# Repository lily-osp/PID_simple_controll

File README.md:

# BLDC Motor PID Controller (ESP32-C3)

Fixed-target PID controller for BLDC motors on the ESP32-C3, run bare-metal
for compute (no WiFi, no BLE). Holds 1440 RPM via a 200Hz FreeRTOS loop.

> History: this project previously shipped Arduino Uno and ATtiny85 variants.
> They were removed on 2026-10-31 (commit `396ade7`) and remain in git history.

## Overview

Single-platform implementation targeting the ESP32-C3 SuperMini. The C3 is
used for its 160MHz RISC-V core and hardware FPU; no wireless stack is used.
Two firmware builds share one set of drivers: a bench build for bring-up and
a production build for the enclosure.

| Build | Status | Use Case | Key Features |
|-------|--------|----------|--------------|
| **`esp32-c3/control/`** | Bench | Bring-up, service, Hall-line trials | Serial console, telemetry, trial scoring |
| **`esp32-c3/embedded/`** | Production | Enclosure deployment | Silent, autonomous, arming + stall failsafe |

## Key Features

- **200Hz Control Loop**: High-frequency PID updates via dedicated FreeRTOS task
- **Hardware-Accelerated PWM**: ESP32 LEDC peripheral generating smooth 5kHz motor control signals
- **Interrupt-Driven RPM**: High-precision pulse counting using IRAM-resident ISR
- **Sliding Window Filter**: 12-sample window + IIR smoothing for stable control input
- **ESC Arming + Soft-Start**: 2s zero-throttle arm, then 1.5s power ramp
- **FPU Utilization**: Full floating-point PID calculations for maximum precision
- **Safety Features**: Stall failsafe, emergency stop, input validation

## Quick Start

### 1. Hardware Requirements

- ESP32-C3 SuperMini (or compatible) + USB-C cable
- 3-Phase BLDC Motor with Hall Effect sensors
- PWM-compatible ESC / motor driver (e.g., JYQD V7.3E)
- Power supply appropriate for motor voltage requirements
- Voltage divider (2.2kΩ/3.3kΩ) if using 5V Hall sensors

### 2. Installation Steps

```bash
git clone https://github.com/your-repo/PID_simple_controll.git
cd PID_simple_controll
```

**Configure for your motor**:
1. Edit `esp32-c3/control/config.h` (pins, motor, PPR)
2. Edit `esp32-c3/control/config_common.h` (PID gains)
3. Configure pin assignments if using custom wiring

**Upload firmware**:
- Use Arduino IDE with ESP32 board support, or `arduino-cli`:

```bash
arduino-cli compile -b esp32:esp32:nologo_esp32c3_super_mini esp32-c3/embedded
arduino-cli upload  -p /dev/ttyACM0 -b esp32:esp32:nologo_esp32c3_super_mini esp32-c3/embedded
```

Which build to flash: see [esp32-c3/BUILDS.md](esp32-c3/BUILDS.md).

## Platform Details

### ESP32-C3 (`esp32-c3/`)

**Processor**: RISC-V @ 160MHz with hardware FPU

**Firmware Builds**:

**Bench (`control/`)**: Serial console for bring-up and service.
- Command parser, telemetry, diagnostics console
- Trial log auto-scores each power cycle to rank Hall permutations
- Full visibility into PID state and RPM estimation

**Production (`embedded/`)**: Silent, autonomous build for the enclosure.
- Control loop, ESC arming, soft-start, stall failsafe
- Shares the exact RPM estimator, PID, and LEDC drivers with the bench build

**Features**:
- Hardware FPU for fast floating-point calculations
- FreeRTOS ensures deterministic timing
- 3.3V logic level (requires voltage divider for 5V sensors)
- Comprehensive debugging via Serial Monitor (bench build)

Full architecture: [esp32-c3/README.md](esp32-c3/README.md).

### Custom Driver PCB (`PCB/V1/`)

Full-integration **64 × 98 mm, 4-layer** board combining the firmware above with its own
driver hardware — no external ESC needed:

- **JYQD-V7.3E3 architecture**: JY01 controller + JY213L gate driver + JY2605M
  half-bridges (same silicon as the reference driver board)
- **ESP32-C3 Super Mini** onboard as the controller (FG/PWM/VR/EL/trim pot)
- **Hall signal conditioner**: RC filter → LM324 (×11) → 74HC14 Schmitt trigger
- **Power tree**: V_IN → 7812 → +12V → 7805 → +5V

Design files, port pinouts, and build scripts: [PCB/V1/README.md](PCB/V1/README.md).
Bring-up procedure: [PCB/V1/TESTPLAN.md](PCB/V1/TESTPLAN.md).

## Documentation

### Comprehensive Guides

- **[Hardware Assembly Guide](docs/howto.md)**: Wiring guide, pin assignments, and connection diagrams
- **[Bench Wiring — stock JYQD + ESP32](docs/bench_wiring.md)**: Run the firmware on a stock JYQD-V7.3E3 and a bare Super Mini, before the custom PCB
- **[Troubleshooting Guide](docs/mitigation.md)**: Comprehensive diagnosis and solutions for common issues
- **[ESP32-C3 README](esp32-c3/README.md)**: Architecture, firmware, and hardware setup
- **[Builds](esp32-c3/BUILDS.md)**: Production vs bench firmware, and how they share code
- **[Diagnostics Guide](esp32-c3/DIAGNOSTICS.md)**: Serial console commands and fault isolation
- **[Driver PCB](PCB/V1/README.md)**: 64 × 98 mm 4-layer ESP32-C3 + JYQD-architecture driver board
- **[PCB Test Plan](PCB/V1/TESTPLAN.md)**: Staged bring-up procedure and failure diagnosis

## Configuration

### Motor Configuration

Settings live in `esp32-c3/*/config.h`:

```cpp
#define PULSES_PER_REV  4     // Set based on motor pole count
#define DEFAULT_TARGET_RPM 1440.0  // Target speed in RPM
```

**Calculating PULSES_PER_REV**: For a motor with N poles using single Hall sensor: `PULSES_PER_REV = N / 2`

Example: 8-pole motor = 4 pulses per revolution

### PID Tuning

PID constants are defined in `esp32-c3/control/config_common.h`:

```cpp
#define DEFAULT_KP  0.150  // Proportional gain
#define DEFAULT_KI  0.080  // Integral gain
#define DEFAULT_KD  0.015  // Derivative gain
```

**Tuning Process**:
1. Begin with Kp only (set Ki and Kd to 0)
2. Increase Kp until oscillation occurs, then reduce by 30%
3. Add Ki gradually to eliminate steady-state error
4. Add small Kd if overshoot occurs
5. Watch the bench console telemetry to verify stability

## Safety Considerations

1. **Electrical Isolation**: Keep logic power separate from motor power (common ground only)
2. **Voltage Protection**: Use voltage dividers when interfacing 5V sensors with 3.3V logic
3. **Mechanical Safety**: Secure motor firmly and remove propellers during initial testing
4. **Emergency Stop**: Keep power disconnect easily accessible during testing
5. **Current Rating**: Ensure power supply can handle motor startup current (typically 2-3x running current)
6. **Thermal Management**: Monitor ESC and motor temperatures during extended operation

## Troubleshooting Quick Reference

| Issue | Likely Cause | Solution |
|-------|--------------|----------|
| Motor doesn't start | Insufficient PWM threshold | Increase `PWM_MIN_THRESHOLD` to 60-80 |
| RPM reading 2x actual | Wrong `PULSES_PER_REV` | Divide current value by 2 |
| Unstable speed | Poor PID tuning or noise | Reduce Kp by 30%, add filtering |
| Random RPM spikes | Electrical noise | Add 0.1µF capacitor to Hall input |
| ESP32-C3 damaged | 5V applied to GPIO | Use voltage divider for all 5V signals |

See [Troubleshooting Guide](docs/mitigation.md) for comprehensive solutions.

## Contributing

Contributions are welcome. Areas of interest:
- Advanced PID algorithms (adaptive, fuzzy logic)
- Enhanced filtering techniques
- PCB designs for production deployment
- Test cases and validation procedures

Please read [CONTRIBUTING.md](CONTRIBUTING.md) for guidelines.

## License

MIT License - See [LICENSE](LICENSE) file for details.

This project is provided as-is for educational and commercial use. No warranty is provided for fitness for any particular purpose.

## Support

- **Issues**: Report bugs and request features via GitHub Issues
- **Discussions**: Ask questions and share experiences in GitHub Discussions
- **Documentation**: Comprehensive guides available in `docs/` directory

## Acknowledgments

Built with focus on reliability, performance, and practical deployment. Tested in real-world applications across multiple motor types and configurations.

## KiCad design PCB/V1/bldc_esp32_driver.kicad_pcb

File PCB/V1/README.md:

# BLDC Motor Driver — JYQD-V7.3E3 Architecture + ESP32-C3 Super Mini + Hall Amp

Custom **64 × 98 mm, 4-layer** PCB (full-integration) based on the **JYQD-V7.3E3** brushless driver
architecture, with an **ESP32-C3 Super Mini** controller and a Hall sensor signal
conditioner (RC filter → LM324 gain ×11 → 74HC14 Schmitt trigger).

> `JYQD-V7.3E3-English.pdf` is a product datasheet (specs + wiring), not a schematic.
> The circuit uses the JY IC family — **JY01** (SOP-16 controller), **JY213L** (TSSOP-20
> 3-phase gate driver), **JY2605M** (DFN-8 dual-NMOS half-bridge) — the same silicon as
> the reference board.

## External interface (fully integrated — 3 connectors only)

Everything else is handled on-board by the ESP32 (speed/direction/enable are driven
internally to the JY01). No control port, no GPIO breakouts.

| Connector | Pins | Function | Pitch |
|---|---|---|---|
| **J5** power | `P+  P−` | +12 V (V_IN) and ground | 5.00 mm (MaiXu MX126) |
| **J6** motor | `MA  MB  MC` | phase A / B / C to BLDC | 5.00 mm (MaiXu MX126) |
| **J3** Hall | `GND  Hc  Hb  Ha  5V` | Hall sensors (powered from 5 V) | 2.54 mm |

## Architecture

```
 V_IN ── 7812 ── +12V ── 7805 ── +5V
   │                │          │
 JY01 ──gate R── JY213L ──gate R── JY2605M ×3 ── phases A/B/C (J6)
   │                │
 Hall amp (5V): RC → LM324(×11) → 74HC14 → JY01 Hall inputs
 ESP32-C3: FG (scaled) / PWM → VR / EL / trim pot
```

- **Power tree**: `V_IN` (J5 P+) → U8 L7812 → `+12V` (gate-driver VCC) → U7 L7805 →
  `+5V` (logic). Hall amp runs on **+5V**, so 74HC14 outputs drive JY01 directly.
- **Current sense**: P− passes through R1 shunt (R005, 2512) to GND; JY01 `Is` sees the
  filtered shunt node (`ISENSE_F` via R36 + C21). *Caveat:* verify scaling against the
  driver's internal sense topology before relying on current limit.

## Design notes

- **78xx regulators**: with 12–36 V input keep `V_IN ≤ 28 V` for dropout/power margin
  (12 V nominal recommended).
- **PWM → VR**: GPIO1 drives the JY01 `VR` node through **R7 (100 Ω)**, directly. The
  JYQD datasheet accepts PWM 1–20 kHz on `VR` and averages it internally, so no level
  shifter is needed. Max drive is 3.3 V of the 0.1–5 V range ≈ 66 % speed.
- **GPIO4 → EL level shift**: EL is pulled up to **+5V** (R33 10 kΩ); GPIO4 drives it
  open-drain through R34 (1 kΩ). Configure GPIO4 as open-drain in firmware. Per the
  JYQD datasheet, EL high/floating **allows** operation and GND forbids it, so the
  motor is enabled by default at power-up.
- **FG scaling**: JY01 FG (5 V) → R4 2.2 k / R5 3.3 k divider → GPIO0 (RPM in, 3.3 V).
- **ESP32 pin usage**: GPIO0=RPM (FG), GPIO1=PWM→VR, GPIO2=**unconnected** (boot
  strapping pin, internal pull-up holds it high), GPIO3=trim ADC (ADC1_CH3),
  GPIO4=EL (open-drain), GPIO5=ERR LED. GPIO6–10/20/21 are spare/unconnected.
- **ERR LED** driven from GPIO5 via R32 (560 Ω); **PWR LED** from +5V via R20 (560 Ω).

## Pre-order audit

Checks performed on the exact fabrication data (`fab/`), all passing:

| Check | Result |
|---|---|
| DRC (`--severity-all`) | 0 violations, 0 unconnected items |
| Schematic parity | 0 genuine (266 cosmetic: root-sheet `/` prefix, footprint lib prefix) |
| Outline closure | closed Edge.Cuts loop, 0 open endpoints, 64.1 × 98.1 mm |
| Pads outside outline | 0 |
| Orphan nets (1 pad) | none |
| Fab files | 11 gerbers (4 copper) + 1 drill (Excellon, metric, decimal) + job file |
| Solder mask | 238 front / 33 rear openings (205 SMD + 29 THT + 4 NPTH); 0.05 mm expansion, 0.10 mm min web |
| Paste | 205 front apertures (1:1 with the SMD pads), none on the rear |

### Electrical fixes applied at audit

- **Bootstrap caps C13–C15 were 10 µF/25 V.** The `VB_x` rail floats on the phase and
  peaks at `V_IN + (V_+12V − V_f)` ≈ **V_IN + 11.3 V**. At the intended 12 V input that
  is 23.3 V (93 % of the rating); at 24 V input it is 35.3 V and the part fails short,
  taking the JY213L with it. Changed to **1 µF/50 V**, which is also the correct
  bootstrap value for this gate charge (droop ≈ Q_g/C ≈ 50 mV/cycle). Footprint
  unchanged (0805).
- **Unrated 0805 caps on rails** were given explicit ratings: `C12 → 10 µF/25 V` (it sits
  on +12 V), `C11/C19/C20 → 100 nF/50 V`.

### Layout changes applied at audit

1. **Trim pot moved off the strapping pin.** `RV1`'s wiper was on `GPIO2`, one of the
   three ESP32-C3 strapping pins (GPIO2/8/9), which must be high or floating at boot. The
   pot pulls it to 0 V at the low end of travel, so a power cycle with the pot turned
   down could enter joint-download boot instead of running firmware. The net now goes to
   `GPIO3` (`ADC1_CH3`, not a strapping pin); only the final 1.31 mm stub was rerouted,
   the 20 mm trunk is untouched. `GPIO2` is left floating, which is exactly the state its
   internal boot pull-up wants.
2. **Firmware followed the pin move.** `POT_SENSITIVITY_PIN` is now 3 and the
   `POT_ENABLE_PIN` gate is gone — the trim is always active and the pot midpoint is
   1.0×. Previously the firmware expected the enable on `GPIO3` while the board left it
   unconnected, so the pot did nothing at all. Both sketches compile (`pio run`,
   espressif32 7.0.1): control 17.9 % flash / 4.3 % RAM, embedded likewise.
3. **Four M3 mounting holes added** at the corner-arc centres (5 mm from each edge),
   NPTH 3.2 mm, marked board-only so they do not appear as schematic-parity extras, with
   a 1.2 mm copper-free ring so a screw head cannot short the GND pour.
4. **`C4` shifted 2.4 mm left** because its 10 mm can sat 0.4 mm from the bottom-right
   hole — an M3 head would have fouled it. Its three track endpoints were snapped to the
   new pad positions; nothing else moved.

### Remaining note

- **`EL` (GPIO4) and the ERR LED (GPIO5) are wired but unused by firmware.** `EL` is
  pulled to +5 V through R33 and driven open-drain through R34, so the JY01 enable state
  at power-up depends on the EL polarity of the JY01 itself — confirm before relying on
  the motor being disabled at boot. Wiring either up is a firmware change only.

## Status

**Folder layout:** `PCB/V1/` is this board. When a smaller revision is attempted it goes
in `PCB/V2/` alongside it, so both stay buildable and comparable.

**The previous board is preserved at git tag `v1`** (commit 837cf5a): 70 × 120 mm,
2 layers. This folder is the current 64 × 98 mm 4-layer board.

| | old (tag `v1`) | this board |
|---|---|---|
| Size | 70 × 120 mm (8400 mm²) | **64 × 98 mm (6272 mm², −25 %)** |
| Layers | 2 | **4** (In1 = solid GND plane) |
| Signal layers | 2 | 3 (F.Cu, In2.Cu, B.Cu) |
| Phase copper (avg) | 0.33–0.39 mm | **0.67–0.74 mm** |
| Traces / vias | 1277 / 142 | 862 / 121 |
| DRC | 0 / 0 | 0 / 0 |

- **Schematic**: complete & verified — netlist matches the design table **223/234 pins**
  (floating pins are the 3 unused 74HC14 gate outputs + 8 spare ESP32 GPIOs).
- **Board**: **fully routed, DRC-clean, fab package generated** — 64.1 mm × 98.1 mm
  (5 mm rounded corners), 92 footprints (67 components + 4 M3 holes + 21 test points).
  - 862 traces, 121 vias, 4 zones (solid GND plane on In1 + GND pours on
    F.Cu / B.Cu / In2.Cu)
  - **DRC: 0 violations, 0 unconnected items** (`kicad-cli pcb drc --severity-all`)
  - **Schematic parity: 0 genuine mismatches** — the 266 reported items are cosmetic only
    (schematic nets carry the root-sheet `/` prefix; footprints are reported without their
    library prefix). Verified programmatically: 0 net-name differences, 0 footprint
    differences after normalisation, 0 extra footprints.
  - **Outline**: closed Edge.Cuts loop, 0 open endpoints; **0 pads outside** the outline.
  - **Drills**: 0.3 mm ×110 and 0.4 mm ×15 (vias), 0.8/1.0/1.1/1.2/1.3 mm ×29
    (component holes), 3.2 mm ×4 (M3 mounting, NPTH).
  - Renders: `render/routed_top.png`, `render/routed_bottom.png`
  - **Bottom silkscreen**: OSP cloud logo (16 mm, vectorised from
    `OSP_1600.png` with potrace into 14 filled polygons) and the credit
    `designed by : github.com/1999azzar`, both on `B.SilkS`.

### Copper sizing (measured, not assumed)

The 4-layer stack gives the phases a dedicated corridor, so they are no longer starved by the 2-layer
clearance wall. Length-weighted averages:

| Net | 2-layer avg | **this board avg** | min | max |
|---|---|---|---|---|
| PH_A | 0.33 mm | **0.75 mm** | 0.25 mm | 0.80 mm |
| PH_B | 0.35 mm | **0.74 mm** | 0.25 mm | 0.80 mm |
| PH_C | 0.39 mm | **0.77 mm** | 0.25 mm | 0.80 mm |
| V_IN | 0.80 mm | **0.79 mm** | 0.65 mm | 0.80 mm |
| PNEG | 0.80 mm | **0.80 mm** | 0.80 mm | 0.80 mm |
| +12V / +5V | 0.57 mm | 0.40 mm | 0.40 mm | 0.40 mm |

> **Current capability.** The phases now run at 0.75 mm average with only short
> (sub-millimetre) necks at the driver's 0.65 mm-pitch pads. On **2 oz outer copper** that
> is roughly **4 A per phase**, up from ~2.6 A on the 2-layer board. The `+12V`/`+5V` rails are thinner
> than v1 (0.40 mm) because they are logic/gate-drive supplies: 0.40 mm on 2 oz carries
> ~1.5 A, and the actual load is a few hundred mA.

## Component placement (64 × 98 mm)

| Zone | Components |
|---|---|
| Top edge | J5 (power in), J6 (motor out), M3 holes in the corners |
| Bottom edge | J3 (Hall port) |
| Left column | C1/C2/C5 bulk → U8 (7812) → C3 → U7 (7805) → C4, i.e. the whole power chain |
| Under J6 | Q2/Q3/Q4 (JY2605M) with R1 shunt |
| Right of the FETs | U3 (JY213L), bootstrap C13–C15 + D1–D3, gate resistors R14–R19 |
| Middle | U1 (JY01) + R8–R13, then the Hall amp (U4 LM324, U5 74HC14, R21–R31) |
| Bottom | U6 (ESP32-C3), RV1, LEDs |

`U3` sits clear of the FET row on purpose: its 0.65 mm-pitch phase-sense pins need a
fanout corridor, and placing it in line with the FETs makes them unreachable.

## Routing pipeline (reproducible)

1. `gen_sch_full.py` — regenerate schematic (netlist-verified).
2. `compact_4l.py` — the placement + 64 × 98 mm rounded outline, with a courtyard
   clash report (`--check` reports without saving).
3. `route_prep_4l.py` — export the DSN and inject width classes. **In1.Cu is set to
   `power`**, so FreeRouting will not put signal traces on it and it stays a solid plane.
4. FreeRouting **2.1.0** on Java 21:
   `java -jar freerouting.jar -de board.dsn -do board.ses -mp 40 -mt 1`
   (single-threaded; the multi-threaded optimizer creates clearance violations).
5. `import_4l.py` — import the session, (re)create the GND plane + pours, refill.
6. `fix_open_nets_4l.py NET...` — rip a few nets and re-route them with everything else
   frozen, when the router leaves a handful open.
7. `silk_4l.py` — hide passive reference designators and clear silkscreen warnings.
8. `fab_package.sh [--2oz]` — gerbers + drill + positions + `fab/ORDER.md`.

**Five things that cost hours, documented so they don't again:**

- KiCad exports a GND pour as a full-board Specctra `(plane ...)` on **every** copper
  layer. If the pours are present during export, FreeRouting sees an occupied board and
  plateaus at ~90+ unrouted. Remove the zones before export, refill afterwards.
- `board.Remove(item)` silently does nothing in this pcbnew build. Use `board.Delete(item)`
  — the failure mode is invisible (the board keeps its old tracks) and costs a full
  routing run to notice.
- FreeRouting can finish routing and then hang before writing the `.ses`. The cause is
  stale `java` processes from earlier runs; `kill -9` every `java` before starting.
- A `0.65 mm`-pitch TSSOP cannot fan out three sense pins into a via between adjacent
  pads. It needs ~3 mm of clear corridor above the pin row; that is what drove the
  power-stage placement.
- On a 4-layer board the zones can end up as several filled islands. Stitch them to the
  In1 plane with GND vias, otherwise DRC reports the pour as unconnected.
- KiCad writes the inner copper layers with their internal layer IDs (`Copper,L5,Inr`,
  `L7`) into the `.gbrjob` even though the gerbers themselves carry the correct `L2`/`L3`.
  `fab_package.sh` rewrites the job file so CAM cannot read a 4-layer stack as 8-layer.
- A 3D render with no model library looks like a bare board with random pads, which reads
  as "the placement is broken". This machine has no `kicad-packages3d` installed; the
  models are fetched with `nix build nixpkgs#kicad.libraries.packages3d` and are shipped
  as **zip files named `.stpZ`**, not zstd. Unzip the ones the board references and point
  `KICAD9_3DMODEL_DIR` at the result:
  `KICAD9_3DMODEL_DIR=<dir> kicad-cli pcb render ...`
  This project's models are installed at `~/.local/share/kicad/3dmodels` and the path is
  registered in `~/.config/kicad/9.0/kicad_common.json`, so a plain render works.
- **U6 (ESP32-C3 SuperMini) has no official 3D model.** It is a third-party board, so it
  is not in the Espressif library (which covers ESP32-C3-MINI-1/WROOM-02 only), and the
  GrabCAD/Printables/SnapEDA models need an account. A dimensionally correct
  representative body (22.5 x 18 x 1.6 mm + USB-C + antenna area) is used instead,
  from `Custom.3dshapes/ESP32-C3-SuperMini.wrl`. It is for visualisation, not mechanical
  clearance work.
- The mask gerbers are emitted as **G36/G37 region fills**, not aperture flashes. Counting
  `%ADD`/`D03` in them reports zero and looks catastrophic; count `G36` instead.

## Ordering

```bash
./tools/fab_package.sh --2oz     # 2 oz outer copper; drop the flag for 1 oz
```

Output in `fab/`:

| File | Contents |
|---|---|
| `bldc_esp32_driver_gerbers.zip` | 11 gerbers (4 copper, 2 mask, 2 silk, 2 paste, Edge.Cuts) + `.drl` |
| `positions.csv` | assembly centroids, mm, drill origin |
| `ORDER.md` | board spec sheet to hand to the fab |

Verification already passed on this exact board: 0 DRC violations, 0 unconnected items,
closed outline, 0 pads outside the outline, 0 genuine schematic-parity mismatches.

### Assembly (PCBA)

The board is set up to be ordered **assembled**, with these deliberately left
unpopulated (marked DNP in both the schematic and the board, so the BOM and CPL
exclude them automatically):

| Ref | Part | Why |
|---|---|---|
| U6 | ESP32-C3 SuperMini | third-party module, fitted by hand |
| J3 | 1x05 2.54 mm header | no headers wanted — wires go straight to the pads |
| J5 | MX126 2-pin terminal | power wires soldered directly |
| J6 | MX126 3-pin terminal | motor wires soldered directly |

**Five parts cannot be bought from LCSC**, so no assembly house that sources
from that catalogue can fit them: **U1 (JY01)**, **U3 (JY213L)** and
**Q2–Q4 (JY2605M)**. They are only sold through Alibaba/AliExpress/specialist
vendors. Either hand-solder them or supply them as consigned parts.

**Test points.** Twenty-one 1.5 mm probe pads are on the top side, each with its
number printed on the silkscreen next to it. They cover the rails (`V_IN`,
`PNEG`, `+12V`, `+5V`, `+3.3V`, `GND`), the control path (`VR`, `ZF`,
`PWM_OUT`, `RPM_IN`, `GPIO4`, `POT_ADC`), the analogue front end (`ISENSE_F`,
`HALL_OUT_B`, `HALL_OUT_C`) and the power stage (`VB_A` and five of the six FET
gates).

Six nets have no pad because the area around them is fully occupied: probe `EL`
at R33 pin 1, `HALL_OUT_A` at U5 pin 2, `GPIO5` at R32 pin 1, `VB_B`/`VB_C` at
C14/C15 pin 1, and `GQ_GH3` at Q4 pin 1. The pads are board-only and excluded
from the BOM/CPL, so they cost nothing. Positions, expected voltages and a staged
bring-up procedure are in [`TESTPLAN.md`](TESTPLAN.md).

The through-hole parts (C1–C5, U7, U8, RV1) are in the CPL, but JLCPCB's
economical PCBA is SMD-only — use their through-hole option or solder those by
hand as well.

`fab/bom_jlcpcb.csv` (27 lines) and `fab/cpl_jlcpcb.csv` (65 placements) are in
JLCPCB's upload format.

**LCSC part numbers: 23 of 26 lines are filled**, each verified against live
LCSC/JLCPCB stock (see `tools/lcsc_map.csv` for the mapping and manufacturer
part). Only these remain blank, and only because LCSC does not carry them:

| Line | Why |
|---|---|
| U1 (JY01), U3 (JY213L), Q2–Q4 (JY2605M) | not in the LCSC catalogue at all |

Values that changed so the parts are actually orderable:

- `C1/C2` are **470 µF/63 V** — 480 µF is not a real capacitor value.
- `C3–C5` are 220 µF/50 V, D10 × 12.5 mm, **5 mm pitch** (matches the D10/P5 land).
- `R1` is a 5 mΩ ±1 % **3 W** 2512 shunt.
- **U2 and R6 are gone.** The old VR interface was an open-drain N-MOSFET with a
  5 V pull-up, which **inverted** the speed control — idle became full speed and the
  PID ran as positive feedback. It was also built around `CSD13380F3`, a 0.73 × 0.64 mm
  TI FemtoFET that cannot sit on the SOT-23-3 land. Both parts were removed and R7 now
  feeds `VR` directly.

> **ERC note**: the schematic reports 28 ERC items, all accounted for — 11 unconnected
> pins are the intentionally-unused 74HC14 gates and spare ESP32 GPIOs; 3 are library
> version/resolution warnings; the rest are power-flag bookkeeping (`V_IN` and the JY01
> `Vss` are fed from external connectors, which ERC wants a `PWR_FLAG` for). None affect
> the manufactured board.

## Files

```
bldc_esp32_driver/
├── bldc_esp32_driver.kicad_sch    # schematic
├── bldc_esp32_driver.kicad_pcb    # board (64 x 98 mm, 4 layers, DRC-clean)
├── bldc_esp32_driver.kicad_pro
├── README.md                      # this file
├── TESTPLAN.md                    # staged bring-up procedure
├── footprints/ESP32-C3-SuperMini.kicad_mod
├── footprints/JY2605M_DFN8_5x6.kicad_mod   # DFN-8 5x6 half-bridge (no exact lib match)
├── render/routed_{top,bottom,top_zoom}.png # refreshed by fab_package.sh
├── fab/                           # gerbers, drill, ORDER.md, BOM + CPL (JLCPCB)
├── tools/gen_sch_full.py, gen_pcb.py, verify_net.py
├── tools/compact_4l.py, route_prep_4l.py, import_4l.py, fix_open_nets_4l.py
├── tools/add_testpoints.py, make_jlcpcb_assembly.py, lcsc_map.csv
├── tools/silk_4l.py, set_values.py, fix_pot_pin_and_holes.py
├── tools/final_{incremental,import_ses,widen,settle,minwidth,silk_cleanup}.py
├── tools/fab_package.sh           # gerbers + BOM/CPL + renders in one shot
├── fp-lib-table
└── fp-info-cache
```

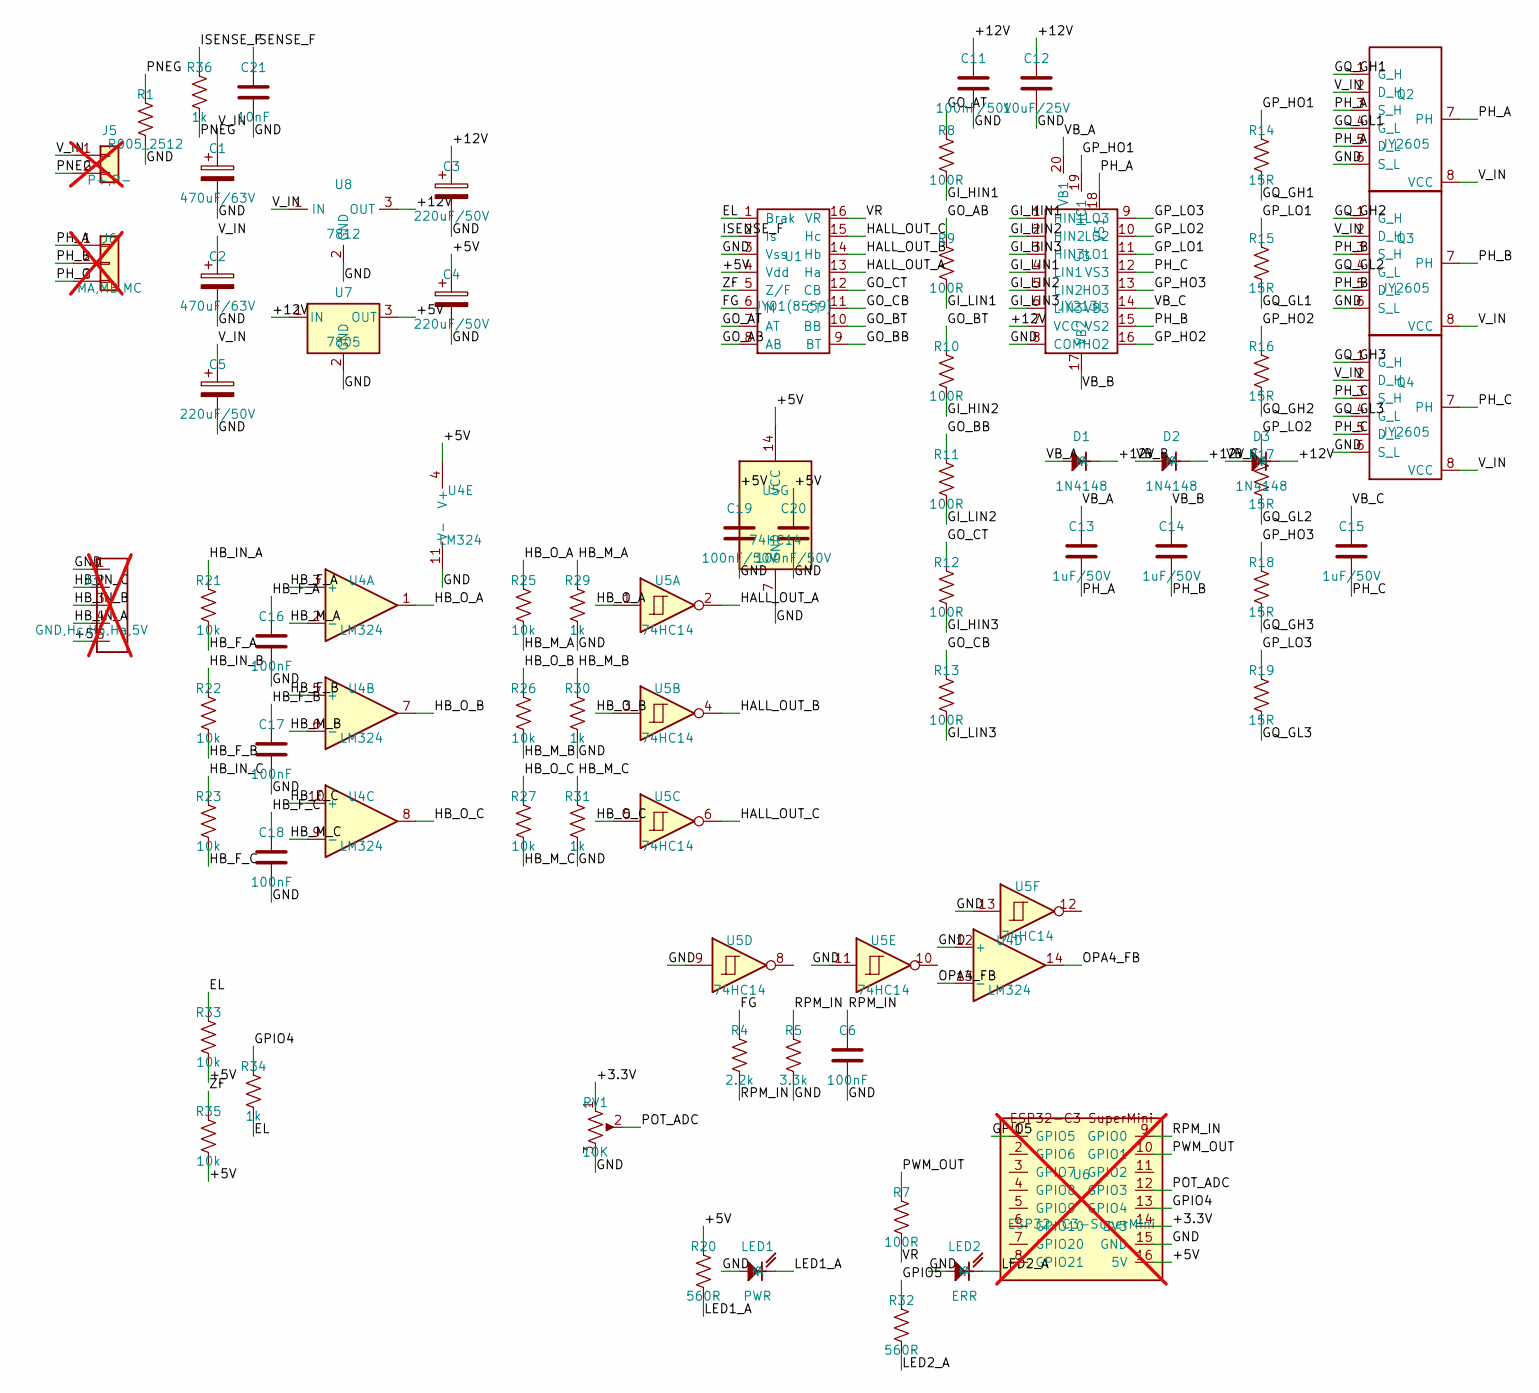
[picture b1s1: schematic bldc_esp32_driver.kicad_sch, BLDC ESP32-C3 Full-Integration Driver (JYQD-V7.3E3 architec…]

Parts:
C1, C2: 470uF/63V; CP_Radial_D13.0mm_P5.00mm
C3, C4, C5: 220uF/50V; CP_Radial_D10.0mm_P5.00mm
C6, C16, C17, C18: 100nF; C_0805_2012Metric
C11, C19, C20: 100nF/50V; C_0805_2012Metric
C12: 10uF/25V; C_0805_2012Metric
C13, C14, C15: 1uF/50V; C_0805_2012Metric
C21: 10nF; C_0805_2012Metric
D1, D2, D3: 1N4148; D_SOD-123
J3: GND,Hc,Hb,Ha,5V; PinHeader_1x05_P2.54mm_Vertical; not fitted
J5: P+,P-; TerminalBlock_MaiXu_MX126-5.0-02P_1x02_P5.00mm; not fitted
J6: MA,MB,MC; TerminalBlock_MaiXu_MX126-5.0-03P_1x03_P5.00mm; not fitted
LED1: PWR; LED_0805_2012Metric
LED2: ERR; LED_0805_2012Metric
Q2, Q3, Q4: JY2605; JY2605M_DFN8_5x6
R1: R005_2512; R_2512_6332Metric
R4: 2.2k; R_0805_2012Metric
R5: 3.3k; R_0805_2012Metric
R7, R8, R9, R10, R11, R12, R13: 100R; R_0805_2012Metric
R14, R15, R16, R17, R18, R19: 15R; R_0805_2012Metric
R20, R32: 560R; R_0805_2012Metric
R21, R22, R23, R25, R26, R27, R33, R35: 10k; R_0805_2012Metric
R29, R30, R31, R34, R36: 1k; R_0805_2012Metric
RV1: 10K; Potentiometer_Bourns_3296W_Vertical
U1: JY01(8559); SOP-16_3.9x9.9mm_P1.27mm
U3: JY213L; TSSOP-20_4.4x6.5mm_P0.65mm
U4: LM324; SOIC-14_3.9x8.7mm_P1.27mm
U5: 74HC14; SOIC-14_3.9x8.7mm_P1.27mm
U6: ESP32-C3-SuperMini; not fitted
U7: 7805; TO-220-3_Vertical
U8: 7812; TO-220-3_Vertical

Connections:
+3.3V: RV1.1, U6.14 (3V3)
+5V: C4.1, C19.1, C20.1, J3.5, R20.1, R33.2, R35.2, U1.4 (Vdd), U4.4 (V+), U5.14 (VCC), U6.16 (5V), U7.3 (OUT)
+12V: C3.1, C11.1, C12.1, D1.2 (A), D2.2 (A), D3.2 (A), U3.7 (VCC), U7.1 (IN), U8.3 (OUT)
EL: R33.1, R34.2, U1.1 (Brak)
FG: R4.1, U1.6 (M)
GI_HIN1: R8.2, U3.1 (HIN1)
GI_HIN2: R10.2, U3.2 (HIN2)
GI_HIN3: R12.2, U3.3 (HIN3)
GI_LIN1: R9.2, U3.4 (LIN1)
GI_LIN2: R11.2, U3.5 (LIN2)
GI_LIN3: R13.2, U3.6 (LIN3)
GND: C1.2, C2.2, C3.2, C4.2, C5.2, C6.2, C11.2, C12.2, C16.2, C17.2, C18.2, C19.2, C20.2, C21.2, J3.1, LED1.1 (K), LED2.1 (K), Q2.6 (S_L), Q3.6 (S_L), Q4.6 (S_L), R1.2, R5.2, R29.2, R30.2, R31.2, RV1.3, U1.3 (Vss), U3.8 (COM), U4.11 (V-), U4.12 (+), U5.7 (GND), U5.9, U5.11, U5.13, U6.15 (GND), U7.2 (GND), U8.2 (GND)
GO_AB: R9.1, U1.8 (AB)
GO_AT: R8.1, U1.7 (AT)
GO_BB: R11.1, U1.9 (BT)
GO_BT: R10.1, U1.10 (BB)
GO_CB: R13.1, U1.11 (CT)
GO_CT: R12.1, U1.12 (CB)
GPIO4: R34.1, U6.13 (GPIO4)
GPIO5: R32.1, U6.1 (GPIO5)
GP_HO1: R14.1, U3.19 (HO1)
GP_HO2: R16.1, U3.16 (HO2)
GP_HO3: R18.1, U3.13 (HO3)
GP_LO1: R15.1, U3.11 (LO1)
GP_LO2: R17.1, U3.10 (LO2)
GP_LO3: R19.1, U3.9 (LO3)
GQ_GH1: Q2.1 (G_H), R14.2
GQ_GH2: Q3.1 (G_H), R16.2
GQ_GH3: Q4.1 (G_H), R18.2
GQ_GL1: Q2.4 (G_L), R15.2
GQ_GL2: Q3.4 (G_L), R17.2
GQ_GL3: Q4.4 (G_L), R19.2
HALL_OUT_A: U1.13 (Ha), U5.2
HALL_OUT_B: U1.14 (Hb), U5.4
HALL_OUT_C: U1.15 (Hc), U5.6
HB_F_A: C16.1, R21.2, U4.3 (+)
HB_F_B: C17.1, R22.2, U4.5 (+)
HB_F_C: C18.1, R23.2, U4.10 (+)
HB_IN_A: J3.4, R21.1
HB_IN_B: J3.3, R22.1
HB_IN_C: J3.2, R23.1
HB_M_A: R25.2, R29.1, U4.2 (-)
HB_M_B: R26.2, R30.1, U4.6 (-)
HB_M_C: R27.2, R31.1, U4.9 (-)
HB_O_A: R25.1, U4.1, U5.1
HB_O_B: R26.1, U4.7, U5.3
HB_O_C: R27.1, U4.8, U5.5
ISENSE_F: C21.1, R36.1, U1.2 (Is)
LED1_A: LED1.2 (A), R20.2
LED2_A: LED2.2 (A), R32.2
OPA4_FB: U4.13 (-), U4.14
PH_A: C13.2, J6.1, Q2.3 (S_H), Q2.5 (D_L), Q2.7 (PH), U3.18 (VS1)
PH_B: C14.2, J6.2, Q3.3 (S_H), Q3.5 (D_L), Q3.7 (PH), U3.15 (VS2)
PH_C: C15.2, J6.3, Q4.3 (S_H), Q4.5 (D_L), Q4.7 (PH), U3.12 (VS3)
PNEG: J5.2, R1.1, R36.2
POT_ADC: RV1.2, U6.12 (GPIO3)
PWM_OUT: R7.1, U6.10 (GPIO1)
RPM_IN: C6.1, R4.2, R5.1, U6.9 (GPIO0)
VB_A: C13.1, D1.1 (K), U3.20 (VB1)
VB_B: C14.1, D2.1 (K), U3.17 (VB2)
VB_C: C15.1, D3.1 (K), U3.14 (VB3)
VR: R7.2, U1.16 (VR)
V_IN: C1.1, C2.1, C5.1, J5.1, Q2.2 (D_H), Q2.8 (VCC), Q3.2 (D_H), Q3.8 (VCC), Q4.2 (D_H), Q4.8 (VCC), U8.1 (IN)
ZF: R35.1, U1.5 (Z/F)

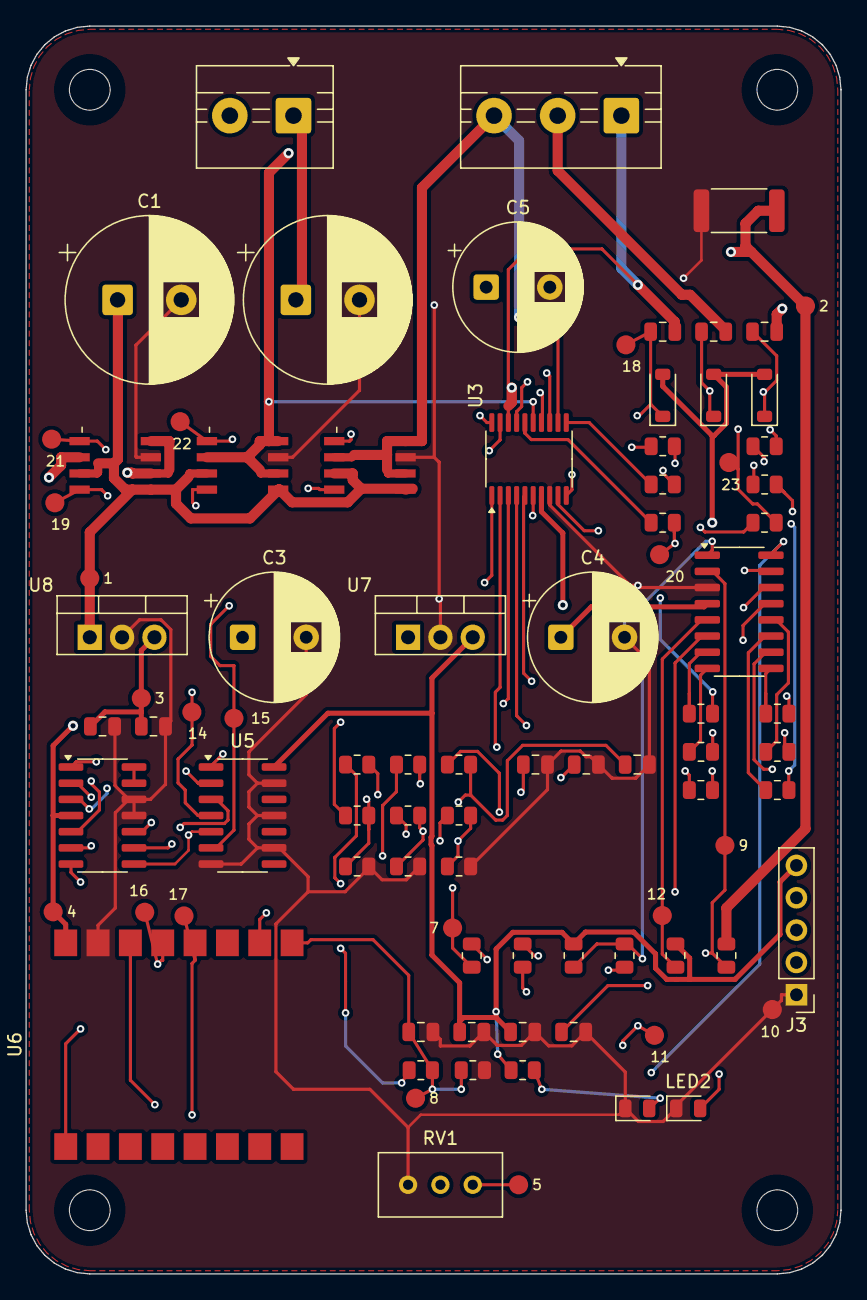
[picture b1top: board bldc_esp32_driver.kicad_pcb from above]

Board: 4 copper layers, 64.0 x 98.0 mm, 92 parts (0 on the bottom side), 64 nets.

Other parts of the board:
H1, H2, H3, H4: MountingHole_3.2mm_M3
TP1, TP2, TP3, TP4, TP5, TP7, TP8, TP9, TP10, TP11, TP12, TP14, TP15, TP16, TP17, TP18, TP19, TP20, TP21, TP22, TP23: (no value)

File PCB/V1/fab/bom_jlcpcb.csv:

Comment,Designator,Footprint,LCSC Part #
470uF/63V,"C1,C2",Capacitor_THT:CP_Radial_D13.0mm_P5.00mm,C47344187
220uF/50V,C3-C5,Capacitor_THT:CP_Radial_D10.0mm_P5.00mm,C165644
100nF,"C6,C16-C18",Capacitor_SMD:C_0805_2012Metric,C49678
100nF/50V,"C11,C19,C20",Capacitor_SMD:C_0805_2012Metric,C49678
10uF/25V,C12,Capacitor_SMD:C_0805_2012Metric,C15850
1uF/50V,C13-C15,Capacitor_SMD:C_0805_2012Metric,C28323
10nF,C21,Capacitor_SMD:C_0805_2012Metric,C1710
1N4148,D1-D3,Diode_SMD:D_SOD-123,C2099
PWR,LED1,LED_SMD:LED_0805_2012Metric,C84256
ERR,LED2,LED_SMD:LED_0805_2012Metric,C84256
JY2605,Q2-Q4,local:JY2605M_DFN8_5x6,
R005_2512,R1,Resistor_SMD:R_2512_6332Metric,C2903482
2.2k,R4,Resistor_SMD:R_0805_2012Metric,C17520
3.3k,R5,Resistor_SMD:R_0805_2012Metric,C204416
100R,R7-R13,Resistor_SMD:R_0805_2012Metric,C17408
15R,R14-R19,Resistor_SMD:R_0805_2012Metric,C20142755
560R,"R20,R32",Resistor_SMD:R_0805_2012Metric,C5576051
10k,"R21-R23,R25-R27,R33,R35",Resistor_SMD:R_0805_2012Metric,C17414
1k,"R29-R31,R34,R36",Resistor_SMD:R_0805_2012Metric,C2073872
10K,RV1,Potentiometer_THT:Potentiometer_Bourns_3296W_Vertical,C34846
JY01(8559),U1,Package_SO:SOP-16_3.9x9.9mm_P1.27mm,
JY213L,U3,Package_SO:TSSOP-20_4.4x6.5mm_P0.65mm,
LM324,U4,Package_SO:SOIC-14_3.9x8.7mm_P1.27mm,C127953
74HC14,U5,Package_SO:SOIC-14_3.9x8.7mm_P1.27mm,C130461
7805,U7,Package_TO_SOT_THT:TO-220-3_Vertical,C111887
7812,U8,Package_TO_SOT_THT:TO-220-3_Vertical,C105651

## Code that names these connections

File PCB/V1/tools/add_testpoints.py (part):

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
# reference to reuse when a pad is being re-placed after a layout change, so the
# numbers already printed in TESTPLAN.md stay valid
PREFER = {"+3.3V": "TP5", "RPM_IN": "TP8", "GPIO5": "TP13"}
MM = 1_000_000
PAD_D = 1.5
PAD_CLEARANCE = 0.30   # pad edge to any other net
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
# nets worth probing during bring-up
TARGETS = ["V_IN", "PNEG", "+12V", "+5V", "+3.3V", "VR", "EL", "ZF",
           "PWM_OUT", "RPM_IN", "ISENSE_F", "GPIO5",
           "HALL_OUT_A", "HALL_OUT_B", "HALL_OUT_C", "GND",
           # second pass: enable chain, analogue front end, power stage
           "GPIO4", "POT_ADC",
           "VB_A", "VB_B", "VB_C",
           "GQ_GH1", "GQ_GH2", "GQ_GH3", "GQ_GL1", "GQ_GL2", "GQ_GL3"]

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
